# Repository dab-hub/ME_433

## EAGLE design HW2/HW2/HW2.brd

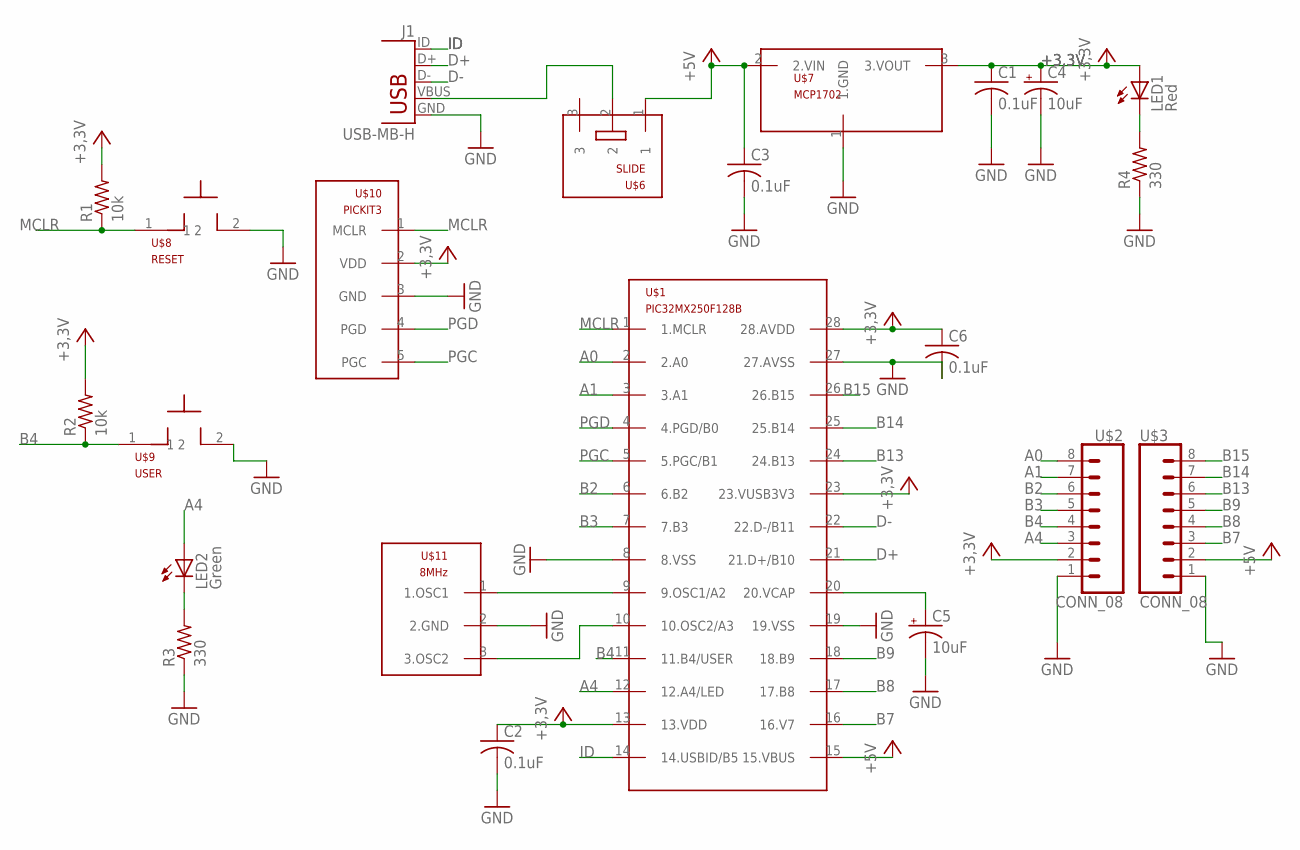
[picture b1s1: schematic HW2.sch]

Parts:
C1, C2, C3, C6: 0.1uF; C025-025X050
C4, C5: 10uF; B45181B
J1: USB-MB-H
LED1: Red; LED3MM
LED2: Green; LED3MM
R1, R2: 10k; 0207/10
R3, R4: 330; 0207/10
U$1: PIC32MX250F128B; DIL28-3
U$2, U$3: CONN_08; 1X08
U$6: SLIDE
U$7: MCP1702; TO92
U$8: RESET; PB
U$9: USER; PB
U$10: PICKIT3; 1X05
U$11: 8MHz; OSC

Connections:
+3,3V: C1.1, C2.1, C4.+, C6.1, LED1.A, R1.2, R2.2, U$1.13 (13.VDD), U$1.23 (23.VUSB3V3), U$1.28 (28.AVDD), U$2.2, U$7.3 (3.VOUT), U$10.2 (VDD)
+5V: C3.1, U$1.15 (15.VBUS), U$3.2, U$6.1, U$7.2 (2.VIN)
A0: U$1.2 (2.A0), U$2.8
A1: U$1.3 (3.A1), U$2.7
A4: LED2.A, U$1.12 (12.A4/LED), U$2.3
B2: U$1.6 (6.B2), U$2.6
B3: U$1.7 (7.B3), U$2.5
B4: R2.1, U$1.11 (11.B4/USER), U$2.4, U$9.1
B7: U$1.16 (16.V7), U$3.3
B8: U$1.17 (17.B8), U$3.4
B9: U$1.18 (18.B9), U$3.5
B13: U$1.24 (24.B13), U$3.6
B14: U$1.25 (25.B14), U$3.7
B15: U$1.26 (26.B15), U$3.8
D+: J1.D+, U$1.21 (21.D+/B10)
D-: J1.D-, U$1.22 (22.D-/B11)
GND: C1.2, C2.2, C3.2, C4.-, C5.-, C6.2, J1.GND, R3.1, R4.1, U$1.8 (8.VSS), U$1.19 (19.VSS), U$1.27 (27.AVSS), U$2.1, U$3.1, U$7.1 (1.GND), U$8.2, U$9.2, U$10.3 (GND), U$11.2 (2.GND)
ID: J1.ID, U$1.14 (14.USBID/B5)
MCLR: R1.1, U$1.1 (1.MCLR), U$8.1, U$10.1 (MCLR)
unnamed: J1.VBUS, U$6.2
unnamed: LED1.K (C), R4.2
unnamed: U$1.9 (9.OSC1/A2), U$11.1 (1.OSC1)
unnamed: U$1.10 (10.OSC2/A3), U$11.3 (3.OSC2)
unnamed: C5.+, U$1.20 (20.VCAP)
unnamed: LED2.K (C), R3.2
PGC: U$1.5 (5.PGC/B1), U$10.5 (PGC)
PGD: U$1.4 (4.PGD/B0), U$10.4 (PGD)

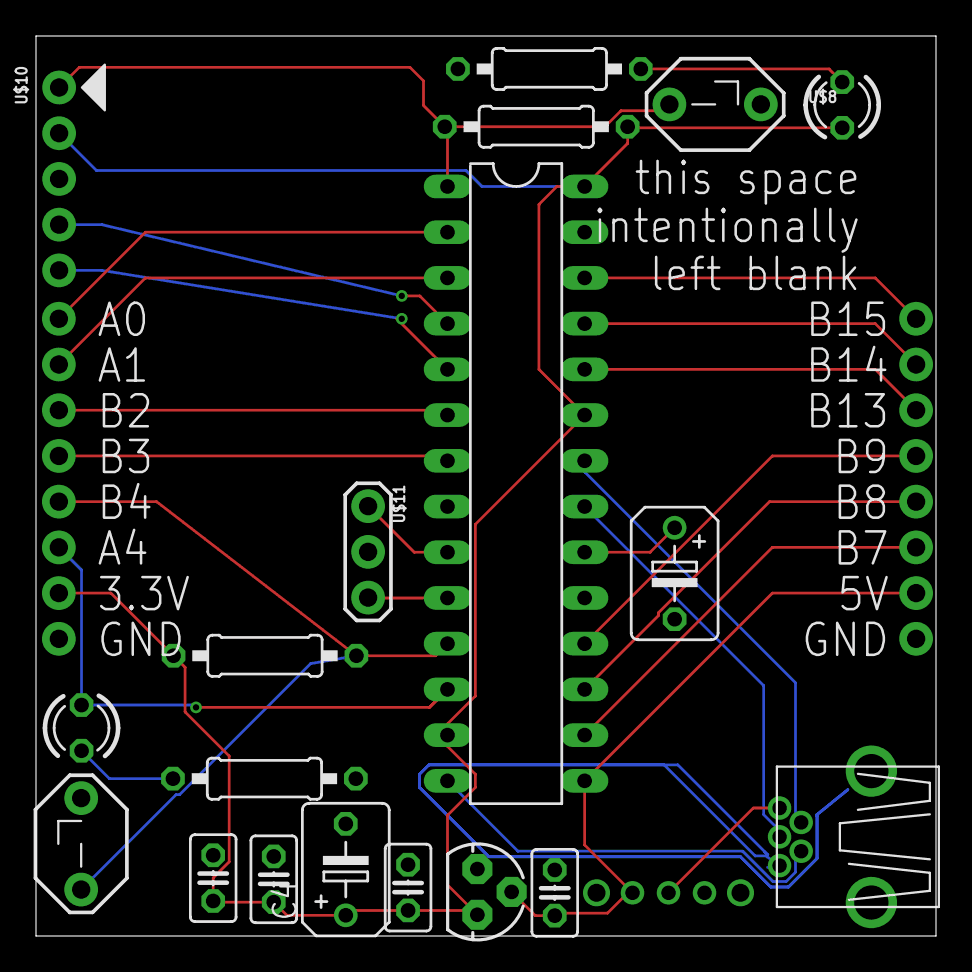
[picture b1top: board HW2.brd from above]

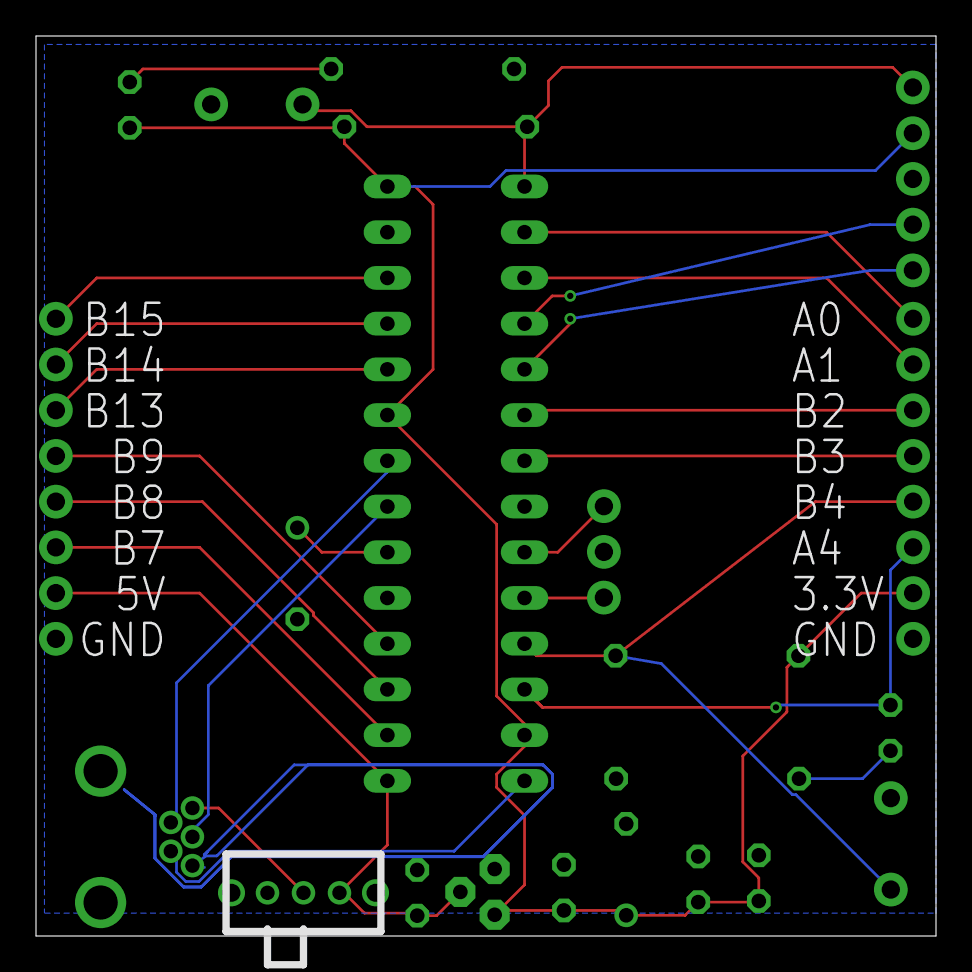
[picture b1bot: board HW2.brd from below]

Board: 2 copper layers, 50.0 x 50.0 mm, 22 parts (2 on the bottom side), 27 nets.

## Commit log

2018-04-08 HW1
    Added config file
    First attempt at while loop
2018-04-08 Photos
    Added photos to repo
2018-04-09 Reorganized Files
    Added everything to "HW1" directory
2018-04-10 Built Library
    built up new parts and collected pre-built parts
2018-04-10 Video
    uploading demo video for hw1
2018-04-10 Finish Schematic
    HW2 complete
2018-04-14 upload gerbers
2018-04-17 Start on HW4
    First steps at programming SPI code
2018-04-18 Updated HW4 code
    added functions: spi_init, spi_io, spi_write, and main while loop
2018-04-18 HW4 Code Final Submit
    Code tested and passed
2018-04-19 upload additional HW4 images
    circuit dia. and oscilliscope output
2018-04-24 HW5 Final Commit
    code done and tested
2018-04-24 Picture/Video upload
2018-04-24 HW6 full commit
2018-05-17 HW7 Full Commit
2018-05-22 commit hw14
2018-05-29 commit hw15
2018-06-05 hw17 commit
2018-06-11 pid control update
2018-06-11 add design photos
